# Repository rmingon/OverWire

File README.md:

# OverWire

**Cut the cord, keep the control.** 
OverWire is a specialized, open-source hardware bridge designed to liberate your STM32 development process. By coupling a powerful ESP32-WROOM-32 module with a dedicated SWD (Serial Wire Debug) interface, OverWire allows you to flash and debug STM32 targets completely wirelessly.

Whether your target is locked inside an enclosure, mounted on a moving robot, or just sitting across the room, OverWire brings the programming interface directly to you over Wi-Fi.

### Real

---
## Features

* **ESP32 at the Core:** Powered by the robust ESP32-WROOM-32 module, providing reliable 2.4 GHz Wi-Fi and Bluetooth connectivity for Over-The-Air (OTA) target flashing.
* **Dedicated SWD Port:** A clean 4-pin header (`3.3V`, `SWCLK`, `SWDIO`, `GND`) ready to hook directly into your STM32 target.
* **USB Type-C Interface:** Modern USB-C connector backed by a CH340C USB-to-UART bridge for painless initial flashing and serial debugging of the ESP32 itself.
* **Auto-Program Circuit:** Features the standard dual-BSS138 (DTR/RTS) auto-reset circuit, meaning you don't need to hold down buttons to flash the ESP32.
* **On-Board LDO:** AMS1117-3.3V regulator safely steps down the 5V USB power to a stable 3.3V for the ESP32 and SWD target.
* **Tactile Control:** Includes `EN` and `BOOT` buttons for the ESP32, plus two programmable user buttons (`TOP1`, `PROGRAM1`) mapped to `IO15` and `IO16` for custom firmware triggers.
* **Status LEDs:** Two user-controllable LEDs mapped to `IO12` and `IO13` for quick visual feedback (e.g., Wi-Fi connected, Flashing target, Error).

## Pinout & Connections

### Target SWD Interface (J3)
| Pin | Name | Description |
| :--- | :--- | :--- |
| 1 | **+3V3** | 3.3V Power Output to target (from AMS1117) |
| 2 | **SWCLK** | Serial Wire Clock (Connects to ESP32) |
| 3 | **SWDIO** | Serial Wire Debug Data I/O (Connects to ESP32) |
| 4 | **GND** | Common Ground |

### Extension / Debug Header (J2)
Provides access to `5V`, `GND`, and the ESP32 UART (`TX-PROG`, `RX-PROG`) for external communication or secondary programming.

## Gallery

### 3D Render

### PCB Layout

### Schematic

## Getting Started

1. Connect OverWire to your PC via a USB Type-C cable.
2. Flash the ESP32 with your preferred wireless SWD firmware (such as a Wi-Fi BlackMagic Probe port or custom TCP-to-SWD bridge).
3. Connect the `J3` SWD header to your STM32 target.
4. Connect to the ESP32 over Wi-Fi and start flashing your STM32 remotely!

---

## License

This hardware design is released under the **Creative Commons Attribution-NonCommercial 4.0 International** (CC BY-NC 4.0) license. 
You are free to view, use, and modify this design for **personal, non-commercial** purposes only. You may **not** use this material for commercial purposes (such as manufacturing and selling the boards) without explicit written permission from the original author.

*Designed with KiCad.*

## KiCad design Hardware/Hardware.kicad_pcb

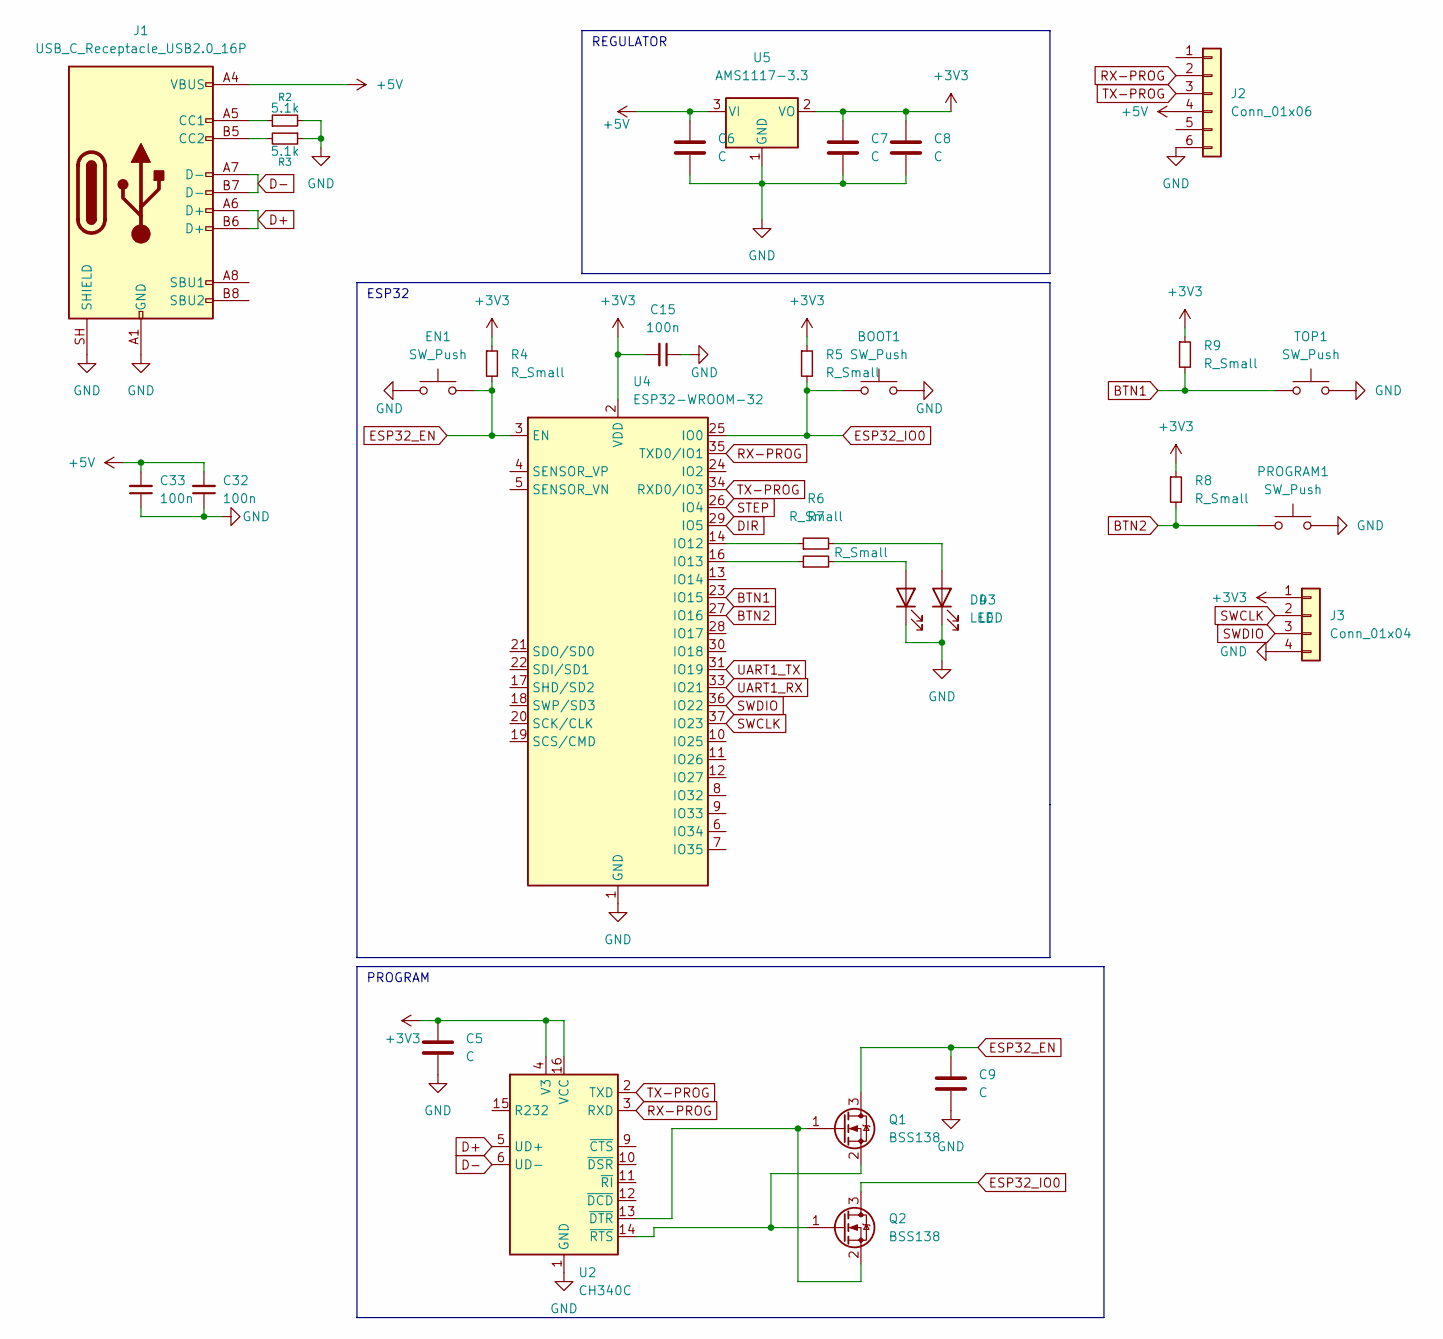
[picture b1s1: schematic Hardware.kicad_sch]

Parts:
BOOT1: SW_Push; SW_Push_SPST_NO_Alps_SKRK; LCSC C398053
C5, C6, C8: C; C_0603_1608Metric; LCSC C30926
C7, C9: C; C_0603_1608Metric; LCSC C19702
C15, C32, C33: 100n; C_1206_3216Metric
D3: LED; LED_0603_1608Metric; LCSC C19171301
D4: LED; LED_0603_1608Metric; LCSC C434425
EN1: SW_Push; SW_Push_SPST_NO_Alps_SKRK; LCSC C398053
J1: USB_C_Receptacle_USB2.0_16P; USB_C_Receptacle_G-Switch_GT-USB-7010ASV
J2: Conn_01x06; PinHeader_1x06_P2.54mm_Vertical
J3: Conn_01x04; PinHeader_1x04_P2.54mm_Horizontal
PROGRAM1: SW_Push; SW_Push_SPST_NO_Alps_SKRK; LCSC C398053
Q1, Q2: BSS138; SOT-23; LCSC C7420338
R2, R3: 5.1k; R_0603_1608Metric
R4, R5, R8, R9: R_Small; R_0603_1608Metric; LCSC C98220
R6, R7: R_Small; R_0603_1608Metric; LCSC C2906975
TOP1: SW_Push; SW_Push_SPST_NO_Alps_SKRK; LCSC C398053
U2: CH340C; SOIC-16_3.9x9.9mm_P1.27mm; LCSC C84681
U4: ESP32-WROOM-32; LCSC C82899
U5: AMS1117-3.3; SOT-223-3_TabPin2; LCSC C6186

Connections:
+3V3: C5.1, C7.1, C8.1, C15.2, J3.1, R4.1, R5.1, R8.1, R9.1, U2.4 (V3), U2.16 (VCC), U4.2 (VDD), U5.2 (VO)
+5V: C6.1, C32.2, C33.2, J1.A4 (VBUS), J1.A9 (VBUS), J1.B4 (VBUS), J1.B9 (VBUS), J2.4, U5.3 (VI)
BTN1: R9.2, TOP1.1, U4.23 (IO15)
BTN2: PROGRAM1.1, R8.2, U4.27 (IO16)
D+: J1.A6 (D+), J1.B6 (D+), U2.5 (UD+)
D-: J1.A7 (D-), J1.B7 (D-), U2.6 (UD-)
DIR: U4.29 (IO5)
ESP32_EN: C9.1, EN1.2, Q1.3 (D), R4.2, U4.3 (EN)
ESP32_IO0: BOOT1.1, Q2.3 (D), R5.2, U4.25 (IO0)
GND: BOOT1.2, C5.2, C6.2, C7.2, C8.2, C9.2, C15.1, C32.1, C33.1, D3.1 (K), D4.1 (K), EN1.1, J1.A1 (GND), J1.A12 (GND), J1.B1 (GND), J1.B12 (GND), J1.SH (SHIELD), J2.6, J3.4, PROGRAM1.2, R2.2, R3.1, TOP1.2, U2.1 (GND), U4.1 (GND), U4.15 (GND), U4.38 (GND), U4.39 (GND), U5.1 (GND)
unnamed: D3.2 (A), R7.2
unnamed: D4.2 (A), R6.2
unnamed: J1.A5 (CC1), R2.1
unnamed: J1.B5 (CC2), R3.2
unnamed: Q1.1 (G), Q2.2 (S), U2.13 (~DTR)
unnamed: Q1.2 (S), Q2.1 (G), U2.14 (~RTS)
unnamed: R6.1, U4.14 (IO12)
unnamed: R7.1, U4.16 (IO13)
RX-PROG: J2.2, U2.3 (RXD), U4.35 (TXD0/IO1)
STEP: U4.26 (IO4)
SWCLK: J3.2, U4.37 (IO23)
SWDIO: J3.3, U4.36 (IO22)
TX-PROG: J2.3, U2.2 (TXD), U4.34 (RXD0/IO3)
UART1_RX: U4.33 (IO21)
UART1_TX: U4.31 (IO19)

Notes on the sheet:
REGULATOR
ESP32
PROGRAM

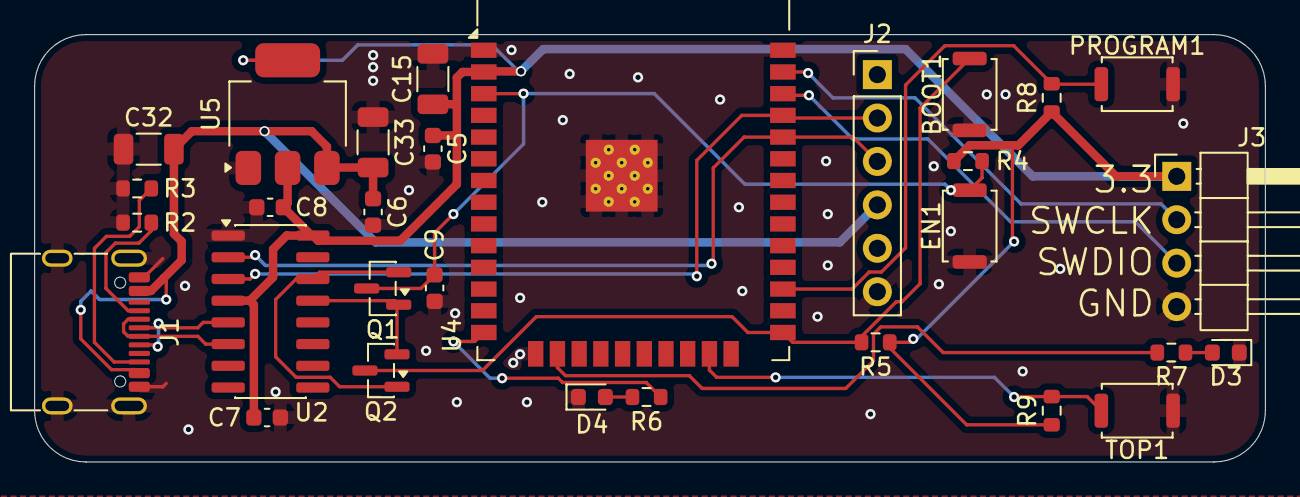
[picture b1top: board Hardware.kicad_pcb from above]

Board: 2 copper layers, 72.0 x 25.0 mm, 30 parts (0 on the bottom side), 21 nets.

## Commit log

2026-05-01 move usb C
2026-05-02 end position pcb
2026-05-02 finish pcb wiring
2026-05-02 add pictures
2026-05-02 add readme
2026-05-02 add license
2026-05-30 add full code for programming
2026-06-18 add rela picture
